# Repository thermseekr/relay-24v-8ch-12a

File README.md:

# RELAY-24V-8CH-12A

Relay board with 8x 24 VDC relays rated for 12A. This board is designed to be used togheter with [ESP-24V-16CH](https://github.com/thermseekr/esp-24v-16ch) and [ESP-24V-32CH](https://github.com/thermseekr/esp-24v-32ch), but can be driven by any 24V control circuit compatible with NPN inputs.

The dimensions are such that the boards can be mounted on a PCB DIN rail holder from the Brazilian manufacturer Metaltex, check [here](https://www.metaltex.com.br/produtos/componentes/suportes/sp7-suporte-para-montagem-de-placa-de-circuito-impresso-em-trilho-din) for details.

Board uses Omron 16A relays and is limited to 12A/channel per copper trace capacity.

## VERSION HISTORY

V1.1 - 2026/06/13 - Input terminal blocks replaced from 2.54mm to 3.5mm pitch for easier installation in the field.

V1.0 - 2024/11/24 - Initial release.

## LICENSE

This project is licensed under the [Creative Commons BY-NC 4.0 License](https://creativecommons.org/licenses/by-nc/4.0/).
Commercial use is not permitted without prior written consent. See the [LICENSE.txt](LICENSE.txt) file for details.

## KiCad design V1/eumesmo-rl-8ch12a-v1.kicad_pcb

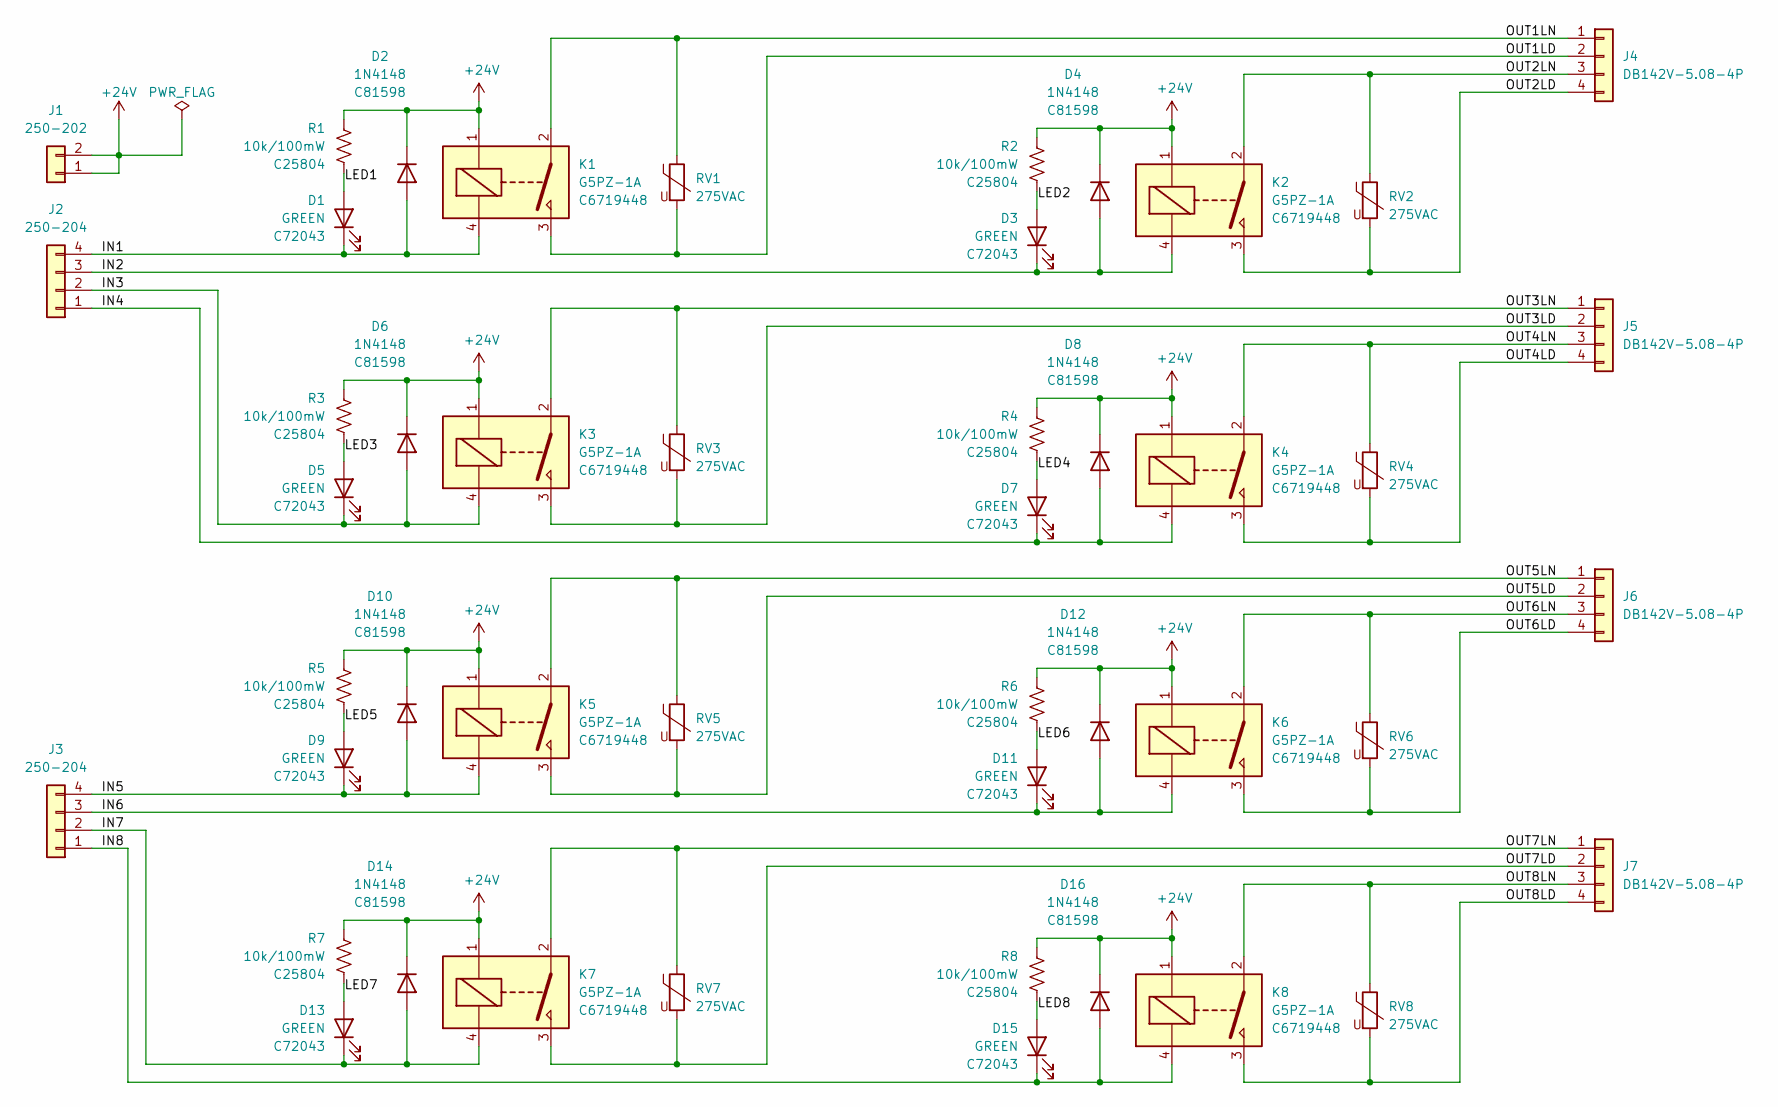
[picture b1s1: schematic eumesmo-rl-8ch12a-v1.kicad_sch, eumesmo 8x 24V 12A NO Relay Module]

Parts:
D1, D3, D5, D7, D9, D11, D13, D15: GREEN; LED_0603_1608Metric; Mfr PN 19-217/GHC-YR1S2/3T; LCSC Part # C72043
D2, D4, D6, D8, D10, D12, D14, D16: 1N4148; D_SOD-123; Mfr PN 1N4148W; LCSC Part # C81598
J1: 250-202; TerminalBlock_Wago_250-202_1x02_P3.5mm_45Degree; Mfr PN 250-202; JLCPCB BOM 1
J2, J3: 250-204; TerminalBlock_Wago_250-204_1x04_P3.5mm_45Degree; Mfr PN 250-204; JLCPCB BOM 1
J4, J5, J6, J7: DB142V-5.08-4P; TerminalBlock_Dibo_DB142V-5.08-4P_1x04_P5.08mm_Vertical; Mfr PN DB142V-5.08-4P-GN; JLCPCB BOM 1
K1, K2, K3, K4, K5, K6, K7, K8: G5PZ-1A; Relay_SPST_Omron_G5PZ-1A; Mfr PN G5PZ-1A-E DC24V; JLCPCB BOM 1
R1, R2, R3, R4, R5, R6, R7, R8: 10k/100mW; R_0603_1608Metric; Mfr PN 0603WAF1002T5E; LCSC Part # C25804
RV1, RV2, RV3, RV4, RV5, RV6, RV7, RV8: 275VAC; RV_Disc_D9.50mm_W3.6mm_P5.08mm; Mfr PN RM07D431KC1IE100; JLCPCB BOM 1

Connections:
+24V: D2.1 (K), D4.1 (K), D6.1 (K), D8.1 (K), D10.1 (K), D12.1 (K), D14.1 (K), D16.1 (K), J1.1, J1.2, K1.1, K2.1, K3.1, K4.1, K5.1, K6.1, K7.1, K8.1, R1.1, R2.1, R3.1, R4.1, R5.1, R6.1, R7.1, R8.1
/IN1: D1.1 (K), D2.2 (A), J2.4, K1.4
/IN2: D3.1 (K), D4.2 (A), J2.3, K2.4
/IN3: D5.1 (K), D6.2 (A), J2.2, K3.4
/IN4: D7.1 (K), D8.2 (A), J2.1, K4.4
/IN5: D9.1 (K), D10.2 (A), J3.4, K5.4
/IN6: D11.1 (K), D12.2 (A), J3.3, K6.4
/IN7: D13.1 (K), D14.2 (A), J3.2, K7.4
/IN8: D15.1 (K), D16.2 (A), J3.1, K8.4
/LED1: D1.2 (A), R1.2
/LED2: D3.2 (A), R2.2
/LED3: D5.2 (A), R3.2
/LED4: D7.2 (A), R4.2
/LED5: D9.2 (A), R5.2
/LED6: D11.2 (A), R6.2
/LED7: D13.2 (A), R7.2
/LED8: D15.2 (A), R8.2
/OUT1LD: J4.2, K1.3, RV1.2
/OUT1LN: J4.1, K1.2, RV1.1
/OUT2LD: J4.4, K2.3, RV2.2
/OUT2LN: J4.3, K2.2, RV2.1
/OUT3LD: J5.2, K3.3, RV3.2
/OUT3LN: J5.1, K3.2, RV3.1
/OUT4LD: J5.4, K4.3, RV4.2
/OUT4LN: J5.3, K4.2, RV4.1
/OUT5LD: J6.2, K5.3, RV5.2
/OUT5LN: J6.1, K5.2, RV5.1
/OUT6LD: J6.4, K6.3, RV6.2
/OUT6LN: J6.3, K6.2, RV6.1
/OUT7LD: J7.2, K7.3, RV7.2
/OUT7LN: J7.1, K7.2, RV7.1
/OUT8LD: J7.4, K8.3, RV8.2
/OUT8LN: J7.3, K8.2, RV8.1

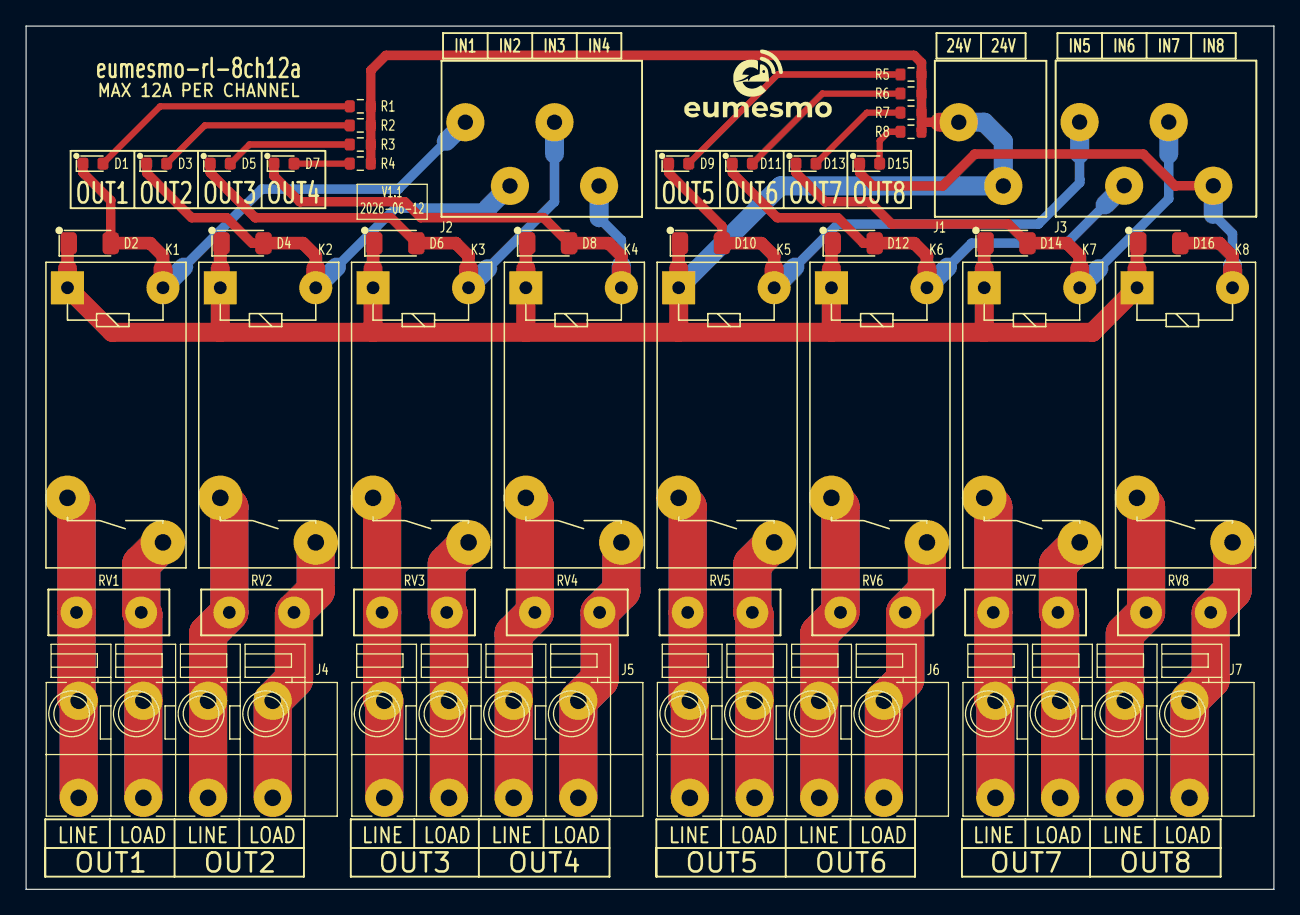
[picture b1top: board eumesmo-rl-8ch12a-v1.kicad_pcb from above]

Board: 2 copper layers, 98.0 x 67.8 mm, 47 parts (0 on the bottom side), 33 nets.

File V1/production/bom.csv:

Designator,Footprint,Quantity,Value,LCSC Part #
"D1, D11, D13, D15, D3, D5, D7, D9",0603,8,GREEN,C72043
"D10, D12, D14, D16, D2, D4, D6, D8",D_SOD-123,8,1N4148,C81598
J1,TerminalBlock_Wago_250-202_1x02_P3.5mm_45Degree,1,250-202,C2765061
"J2, J3",TerminalBlock_Wago_250-204_1x04_P3.5mm_45Degree,2,250-204,C2765063
"J4, J5, J6, J7",TerminalBlock_Dibo_DB142V-5.08-4P_1x04_P5.08mm_Vertical,4,DB142V-5.08-4P,C2898701
"K1, K2, K3, K4, K5, K6, K7, K8",Relay_SPST_Omron_G5PZ-1A,8,G5PZ-1A,C6719448
"R1, R2, R3, R4, R5, R6, R7, R8",0603,8,10k/100mW,C25804
"RV1, RV2, RV3, RV4, RV5, RV6, RV7, RV8",RV_Disc_D9.50mm_W3.6mm_P5.08mm,8,275VAC,C2761646

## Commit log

2025-12-13 Review before fabrication
2025-12-19 Revising before manufacturing.
2026-06-12 Replaced input terminal blocks for 3.5mm pitch.
2026-06-13 Renamed all files to match the eumesmo branding.
2026-06-14 Adjusted version numbers.
